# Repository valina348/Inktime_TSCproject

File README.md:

# InkTime Smartwatch

> An open-source, low-cost smartwatch built around the nRF52840 SoC and an e-paper display.

---

## Block Diagram

```
                        ┌─────────────────────────────────────────────────────┐
                        │                   nRF52840 (U1)                     │
                        │              ARM Cortex-M4F @ 64 MHz                │
                        │           BLE 5.0 | USB 2.0 FS | SWD               │
                        └──┬──────┬──────┬──────┬──────┬──────┬──────┬───────┘
                           │ SPI  │ I2C  │ I2C  │ I2C  │ I2C  │GPIO  │ USB
                           │      │      │      │      │      │      │
              ┌────────────┘      │      │      │      │      │      └──────────────┐
              │                   │      │      │      │      │                     │
        ┌─────▼──────┐     ┌──────▼─┐ ┌─▼────┐ │  ┌───▼───┐  │              ┌─────▼──────┐
        │  WSH-12561 │     │BMA421  │ │MAX   │ │  │DRV2605│  │              │KH-TYPE-C   │
        │  E-Paper   │     │  IMU   │ │17048 │ │  │Haptic │  │              │  USB-C     │
        │  Display   │     │ 6-axis │ │Fuel  │ │  │Driver │  │              │ Connector  │
        └────────────┘     └────────┘ │Gauge │ │  └───┬───┘  │              └─────┬──────┘
                                      └──────┘ │      │      │                    │
                                               │  ┌───▼───┐  │              ┌─────▼──────┐
                                               │  │FIT0774│  │              │USBLC6-2SC6Y│
                                        I2C    │  │ ERM   │  │              │ESD Protect │
                                        │      │  │ Motor │  │              └─────┬──────┘
                                        │      │  └───────┘  │                    │
                                  ┌─────▼──────────────────┐ │              ┌─────▼──────┐
                                  │    BQ25180YBGR         │ │              │   VBUS     │
                                  │    LiPo Charger        │◄┘              │  detect    │
                                  └─────┬──────────────────┘                └────────────┘
                                        │
                              ┌─────────▼──────────┐
                              │  AKY0106 LiPo Bat  │
                              │  400 mAh / 3.7V    │
                              └─────────┬──────────┘
                                        │ VBAT
                              ┌─────────▼──────────┐
                              │   RT6160AWSC        │
                              │   Boost Converter   │
                              │  (EPD HV supply)    │
                              └─────────────────────┘

External:
  32.768 kHz Crystal ──► nRF52840 (LFXO — RTC)
  2450AT18B100E Ant  ──► nRF52840 (RF pin, via matching network)
  TC2030-IDC         ──► nRF52840 (SWD debug)
  3x Tactile Buttons ──► nRF52840 (GPIO, active low)
```

---

## Bill of Materials (BOM)

| Ref | Component | Description | Package | Qty | JLCPCB | Datasheet |
|-----|-----------|-------------|---------|-----|--------|-----------|
| U1 | nRF52840-QIAA | MCU, BLE 5.0, ARM Cortex-M4F, 1MB Flash, 256KB RAM | QFN-73 | 1 | [C190794](https://jlcpcb.com/partdetail/NordicSemiconductor-nRF52840_QIAA/C190794) | [Datasheet](https://infocenter.nordicsemi.com/pdf/nRF52840_PS_v1.7.pdf) |
| U2 | BQ25180YBGR | LiPo charger, I2C, 1A, integrated power path | DSBGA-9 | 1 | [C2678722](https://jlcpcb.com/partdetail/TexasInstruments-BQ25180YBGR/C2678722) | [Datasheet](https://www.ti.com/lit/ds/symlink/bq25180.pdf) |
| U3 | MAX17048G+T10 | Fuel gauge, 1% SOC accuracy, I2C | SOT-23-6 | 1 | [C82344](https://jlcpcb.com/partdetail/MaximIntegrated-MAX17048G_T10/C82344) | [Datasheet](https://datasheets.maximintegrated.com/en/ds/MAX17048-MAX17049.pdf) |
| U4 | RT6160AWSC | DC/DC boost converter for EPD supply | SOT-23-6 | 1 | [Search RT6160AWSC](https://jlcpcb.com/parts/componentSearch?searchTxt=RT6160AWSC) | [Datasheet](https://www.richtek.com/assets/product_file/RT6160A/DS6160A-00.pdf) |
| U5 | DRV2605YZFR | Haptic driver, I2C, LRA/ERM support | DSBGA-16 | 1 | [C2062186](https://jlcpcb.com/partdetail/TexasInstruments-DRV2605YZFR/C2062186) | [Datasheet](https://www.ti.com/lit/ds/symlink/drv2605.pdf) |
| IC1 | BMA421 | 6-axis IMU, accelerometer + gyroscope, I2C | LGA-12 | 1 | [Search BMA421](https://jlcpcb.com/parts/componentSearch?searchTxt=BMA421) | [Datasheet](https://www.bosch-sensortec.com/media/boschsensortec/downloads/datasheets/bst-bma421-ds000.pdf) |
| IC2 | USBLC6-2SC6Y | USB ESD protection | SOT-363 | 1 | [C2827654](https://jlcpcb.com/partdetail/STMicroelectronics-USBLC6_2SC6Y/C2827654) | [Datasheet](https://www.st.com/resource/en/datasheet/usblc6-2.pdf) |
| J1 | KH-TYPE-C-16P | USB-C connector, 16-pin | SMD | 1 | [Search KH-TYPE-C-16P](https://jlcpcb.com/parts/componentSearch?searchTxt=KH-TYPE-C-16P) | - |
| J2 | TC2030-IDC | Tag-Connect SWD debug connector, 10-pin | THT | 1 | - | [Datasheet](https://www.tag-connect.com/wp-content/uploads/bsk-pdf-manager/TC2030-IDC_1.pdf) |
| ANT1 | 2450AT18B100E | 2.4 GHz chip antenna, 50 Ω | SMD | 1 | [Search 2450AT18B100E](https://jlcpcb.com/parts/componentSearch?searchTxt=2450AT18B100E) | [Datasheet](https://www.johansontechnology.com/datasheets/2450AT18B100E/2450AT18B100E.pdf) |
| L1 | FTC252012SR47MBCA | Power inductor 4.7 µH | 1008 | 1 | [Search FTC252012SR47M](https://jlcpcb.com/parts/componentSearch?searchTxt=FTC252012SR47M) | - |
| L2 | - | Inductor 10 µH (DC/DC) | 0402 | 1 | - | - |
| L3 | - | Inductor 15 nH (RF matching) | 0402 | 1 | - | - |
| L7 | - | Inductor 3.9 nH (antenna matching) | 0402 | 1 | - | - |
| M1 | DFRobot FIT0774 | ERM haptic motor (shaker) | - | 1 | - | [Datasheet](https://wiki.dfrobot.com/Vibration_Motor_SKU__FIT0774) |
| BAT1 | AKY0106 | LiPo battery 400 mAh, 3.7V | - | 1 | - | - |
| DSP1 | WSH-12561 | E-paper display, SPI interface | - | 1 | - | - |
| X1 | - | Crystal 32.768 kHz | SMD | 1 | - | - |
| SW1–SW3 | - | Tactile push button | SMD | 3 | - | - |
| R1–Rn | - | Resistors, various values | 0201 | - | - | - |
| C1–Cn | - | Capacitors ≤100nF → 0201, >100nF → 0402 | 0201/0402 | - | - | - |

---

## Hardware Description

### MCU — nRF52840 (U1)

The nRF52840 is the central processing unit of InkTime. It integrates:

- ARM Cortex-M4F running at 64 MHz with hardware FPU
- Bluetooth Low Energy 5.0 (used for time synchronization and smartphone notifications)
- USB 2.0 Full Speed (charging detection and firmware updates over DFU)
- 1 MB Flash / 256 KB RAM
- Multiple hardware peripherals: SPI, I2C, UART, ADC, PWM, RTC

All peripherals connect directly to the nRF52840:
- **SPI** — e-paper display (WSH-12561)
- **I2C** — IMU (BMA421), fuel gauge (MAX17048), LiPo charger (BQ25180), haptic driver (DRV2605)
- **GPIO** — buttons, EPD control lines, interrupt lines, HAPTIC_EN

A 32.768 kHz crystal (X1) is connected to XL1/XL2 pins to drive the internal low-frequency oscillator (LFXO), used for the real-time clock (RTC) and sleep timers with µA-level current consumption.

---

### Power Path

```
USB-C (VBUS 5V)
    └──► BQ25180YBGR (LiPo charger, up to 1A)
              ├──► AKY0106 LiPo Battery (400 mAh, 3.7V)
              └──► 3.3V rail (VREG) ──► nRF52840 + all peripherals

VBAT (3.7V from battery)
    └──► RT6160AWSC (boost converter)
              └──► EPD high-voltage supply (PREVGH, PREVGL, GDR, VCOM)
```

**BQ25180YBGR** manages LiPo charging with integrated power path — the system can run from USB while simultaneously charging the battery. It communicates with the MCU over I2C and raises the `PMIC_INT` line on fault or status events (charge complete, overtemperature, etc.).

**RT6160AWSC** is a boost converter that generates the higher voltages required by the e-paper display driver circuit. The EPD requires both positive and negative rail voltages (PREVGH ≈ +20V, PREVGL ≈ −20V) for bistable switching of the electrophoretic ink particles.

**MAX17048G+T10** is a ModelGauge fuel gauge that estimates battery state-of-charge (SOC) with 1% accuracy using a single-cell LiPo model, communicating over I2C. It raises an `ALERT` interrupt when the battery falls below a programmable low-threshold.

---

### E-Paper Display — WSH-12561

The e-paper display uses SPI communication plus 3 control GPIO lines:

| Signal | Direction | Description |
|--------|-----------|-------------|
| SCK | MCU → EPD | SPI clock |
| MOSI | MCU → EPD | SPI data (write only) |
| EPD_CS | MCU → EPD | Chip select (active low) |
| EPD_DC | MCU → EPD | Data / Command select |
| EPD_RST | MCU → EPD | Hardware reset (active low) |
| EPD_BUSY | EPD → MCU | Busy flag — MCU must wait before next command |

The EPD drive circuit (powered by RT6160AWSC boost converter) generates PREVGH, PREVGL, and GDR voltages needed to drive the bistable ink display. A MOSFET (Q3 — DMG2305UX) gates the EPD power supply so it can be fully cut when the display is not refreshing, saving power.

E-paper is chosen for InkTime because it consumes power **only during refresh** (not while displaying a static image), making it ideal for a low-power wearable.

---

### IMU — BMA421

6-axis inertial measurement unit connected via I2C at 400 kHz. Provides:
- 3-axis accelerometer — step counting, gesture detection, tilt/orientation
- 3-axis gyroscope — motion tracking, wrist-raise detection
- Two interrupt lines (`IMU_INT1`, `IMU_INT2`) for wake-on-motion and data-ready events

The IMU is configured for I2C mode by pulling `CSB` high (to 3V3). The I2C address is set via the `SDO` pin (GND = 0x18, 3V3 = 0x19).

---

### Haptic Feedback — DRV2605 + FIT0774

The DRV2605YZFR haptic driver controls the FIT0774 ERM (eccentric rotating mass) vibration motor. It connects to the MCU over I2C and is enabled via the `HAPTIC_EN` GPIO. The driver supports 124 built-in haptic waveform effects (notification patterns, alerts, confirmations) without requiring MCU intervention during playback.

---

### USB — KH-TYPE-C-16P + USBLC6-2SC6Y

USB-C connector with USBLC6-2SC6Y ESD protection on D+ and D− lines. CC1 and CC2 pins each have a 5.1 kΩ pull-down resistor to GND, which is mandatory for USB-C devices to be recognized as UFP (Upstream Facing Port / device) by USB-C chargers and hosts.

The nRF52840 detects VBUS presence via a GPIO to hand off charging control to the BQ25180. USB D+/D− connect directly to the nRF52840's integrated USB transceiver for DFU (Device Firmware Update) support.

---

### Antenna — 2450AT18B100E

2.4 GHz chip antenna placed at the edge of the PCB. Design rules followed:
- No copper pours (ground plane or power planes) under the antenna keepout area
- No signal traces routed under the antenna
- PCB cutout under the antenna to reduce parasitic capacitance to ground
- Pi-network impedance matching (inductor + two capacitors) between the nRF52840 RF pin and the antenna feed, targeting 50 Ω impedance match at 2.4 GHz

---

### SWD Debug — TC2030-IDC

Tag-Connect TC2030-IDC footprint for in-circuit programming and debugging. No physical connector is soldered — a spring-loaded probe clips onto the 6 pads. Test pads are exposed and labeled in silkscreen:

| Test Pad | Signal |
|----------|--------|
| TP_SWDIO | SWDIO |
| TP_SWDCLK | SWDCLK |
| TP_RESET | RESET |
| TP_3.3V | 3V3 |
| TP_GND | GND |
| TP_SWO | SWO (trace output) |

---

## nRF52840 Pin Assignment

| Pin | Net | Connected To | Interface | Notes |
|-----|-----|--------------|-----------|-------|
| P0.00 | XL1 | 32.768 kHz crystal | LFXO | Low-frequency clock for RTC |
| P0.01 | XL2 | 32.768 kHz crystal | LFXO | Low-frequency clock for RTC |
| P0.09 | RF/ANT | Antenna matching network → ANT1 | RF | Dedicated RF pin — PCB cutout required |
| P0.13 | BTN1 | Tactile button SW_UP | GPIO | Active low, 10K pull-up, 1µF debounce |
| P0.14 | BTN2 | Tactile button SW_DN | GPIO | Active low, 10K pull-up, 1µF debounce |
| P0.26 | BTN3 | Tactile button SW_ENT | GPIO | Active low, 10K pull-up, 1µF debounce |
| P0.xx | SDA | BMA421, MAX17048, BQ25180, DRV2605 | I2C | Shared bus, 4.7 kΩ pull-up to 3V3 |
| P0.xx | SCL | BMA421, MAX17048, BQ25180, DRV2605 | I2C | Shared bus, 4.7 kΩ pull-up to 3V3 |
| P1.xx | SCK | E-paper display (WSH-12561) | SPI | |
| P1.xx | MOSI | E-paper display (WSH-12561) | SPI | |
| P1.xx | EPD_CS | E-paper chip select | GPIO | Active low |
| P1.xx | EPD_DC | E-paper data/command | GPIO | High = data, Low = command |
| P1.xx | EPD_RST | E-paper reset | GPIO | Active low |
| P1.xx | EPD_BUSY | E-paper busy flag | GPIO input | MCU polls or uses interrupt |
| P1.xx | HAPTIC_EN | DRV2605 enable | GPIO | Active high |
| P1.xx | PMIC_INT | BQ25180 interrupt | GPIO input | Active low, fault/status events |
| P1.xx | IMU_INT1 | BMA421 interrupt 1 | GPIO input | Wake-on-motion |
| P1.xx | IMU_INT2 | BMA421 interrupt 2 | GPIO input | Data ready |
| P1.xx | ALERT | MAX17048 alert | GPIO input | Low battery threshold |
| SWDIO | SWDIO | TC2030 pin 2 / TP_SWDIO | SWD | Programming & debug |
| SWDCLK | SWDCLK | TC2030 pin 4 / TP_SWDCLK | SWD | Programming & debug |
| D+ | D+ | USB-C D+ (via USBLC6 ESD) | USB | Full-speed USB transceiver |
| D− | D− | USB-C D− (via USBLC6 ESD) | USB | Full-speed USB transceiver |
| VBUS | VBUS | USB-C VBUS detect | GPIO input | 5V presence detection |

> **Note:** Pins marked `P0.xx` / `P1.xx` are assigned in firmware and will be finalized in the GNG revision. The I2C bus is shared between BMA421, MAX17048, BQ25180, and DRV2605 — each has a unique I2C address.

---

## Power Consumption Estimates

| State | Active Components | Estimated Current |
|-------|-------------------|-------------------|
| Deep sleep | nRF52840 RTC only | ~3 µA |
| BLE advertising | MCU + BLE radio | ~3 mA avg |
| E-paper refresh | MCU + EPD + boost converter | ~30 mA peak (1–2 s) |
| IMU active | MCU + IMU | ~1.5 mA |
| Full operation (BLE + EPD + IMU) | All | ~35 mA peak |

**Battery life estimate** (400 mAh, typical usage: BLE advertising + sleep + 1 EPD refresh/min):

```
Average current ≈ 3 mA (BLE) × 10% duty + 3 µA × 90% + 30 mA × (2s/60s)
               ≈ 0.3 mA + 0.003 mA + 1 mA
               ≈ ~1.3 mA average

Battery life ≈ 400 mAh / 1.3 mA ≈ ~13 days
```

---

## Design Log

### PCB Design Decisions

- **4-layer stackup** used to allow a dedicated ground plane on an inner layer, improving RF performance and reducing EMI near the BLE antenna.
- **Antenna placement** at the top edge of the PCB with a copper-free keepout zone and PCB cutout beneath it, per the 2450AT18B100E datasheet recommendations.
- **Decoupling capacitors** (100 nF, 0201) placed as close as possible to each VDD/VDDH/DEC pin of the nRF52840, per Nordic's hardware design guide.
- **Via stitching** applied between top and bottom ground planes, especially around the RF section, to minimize ground impedance at RF frequencies.
- **All components placed on TOP layer** only, as required by the project specification.
- **Power traces** routed at 0.3 mm width (VCC, VBUS, VBAT, 3V3); signal traces at minimum 0.15 mm.
- **No right-angle bends** on any trace — all routing uses 45° angles.
- **USB-C CC resistors** (5.1 kΩ to GND on CC1 and CC2) ensure correct USB-C device recognition by any standard charger.
- **Battery connected directly to test pads** (TP_VBAT, TP_BAT_GND) on the PCB instead of using the JST connector, to save vertical space inside the enclosure.

### Known Accepted Errors

- DRC "Dimension" errors caused by the placement of the three tactile buttons and the USB-C connector at the PCB edge — these are by design to align with the physical openings in the enclosure and are accepted per project specification.
- ERC warning "Only INPUT pins on NET ID" — accepted per project specification (known Fusion360 library artifact).

---

## License

This project is licensed under the **Apache License 2.0**.

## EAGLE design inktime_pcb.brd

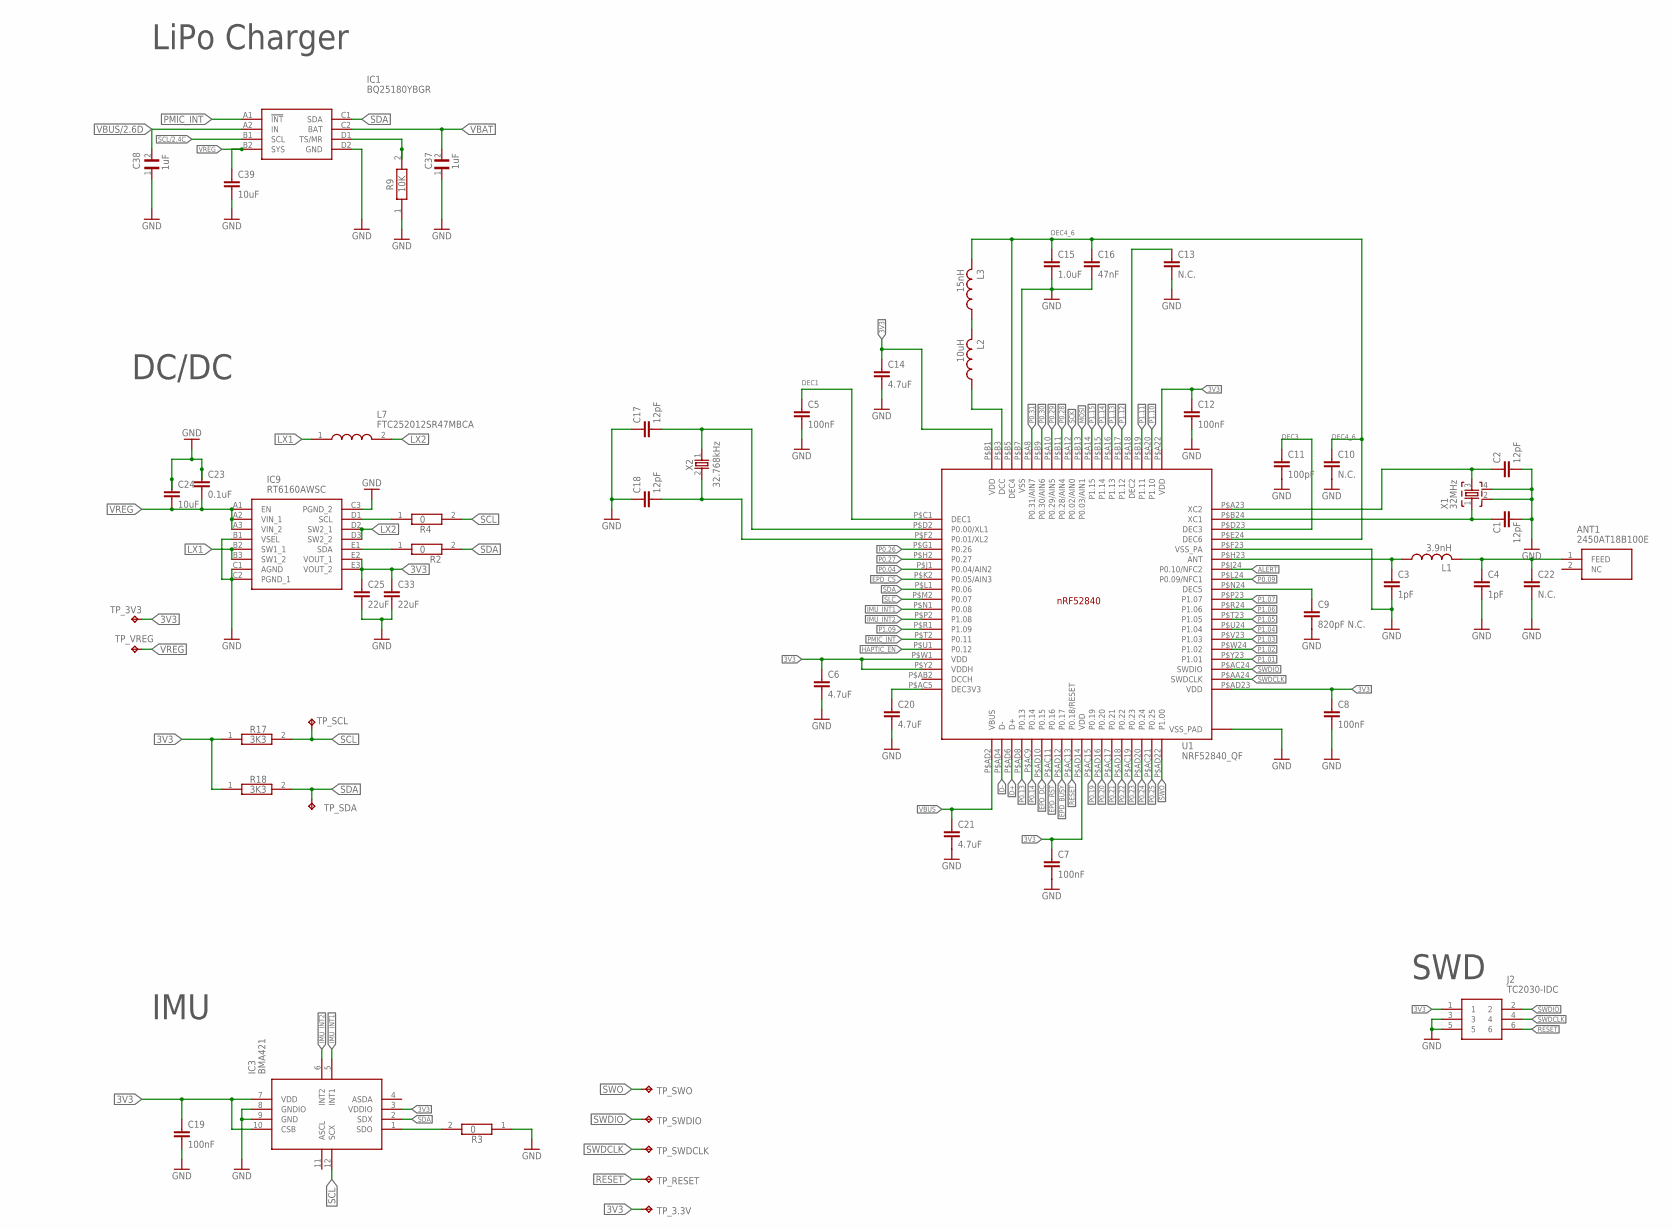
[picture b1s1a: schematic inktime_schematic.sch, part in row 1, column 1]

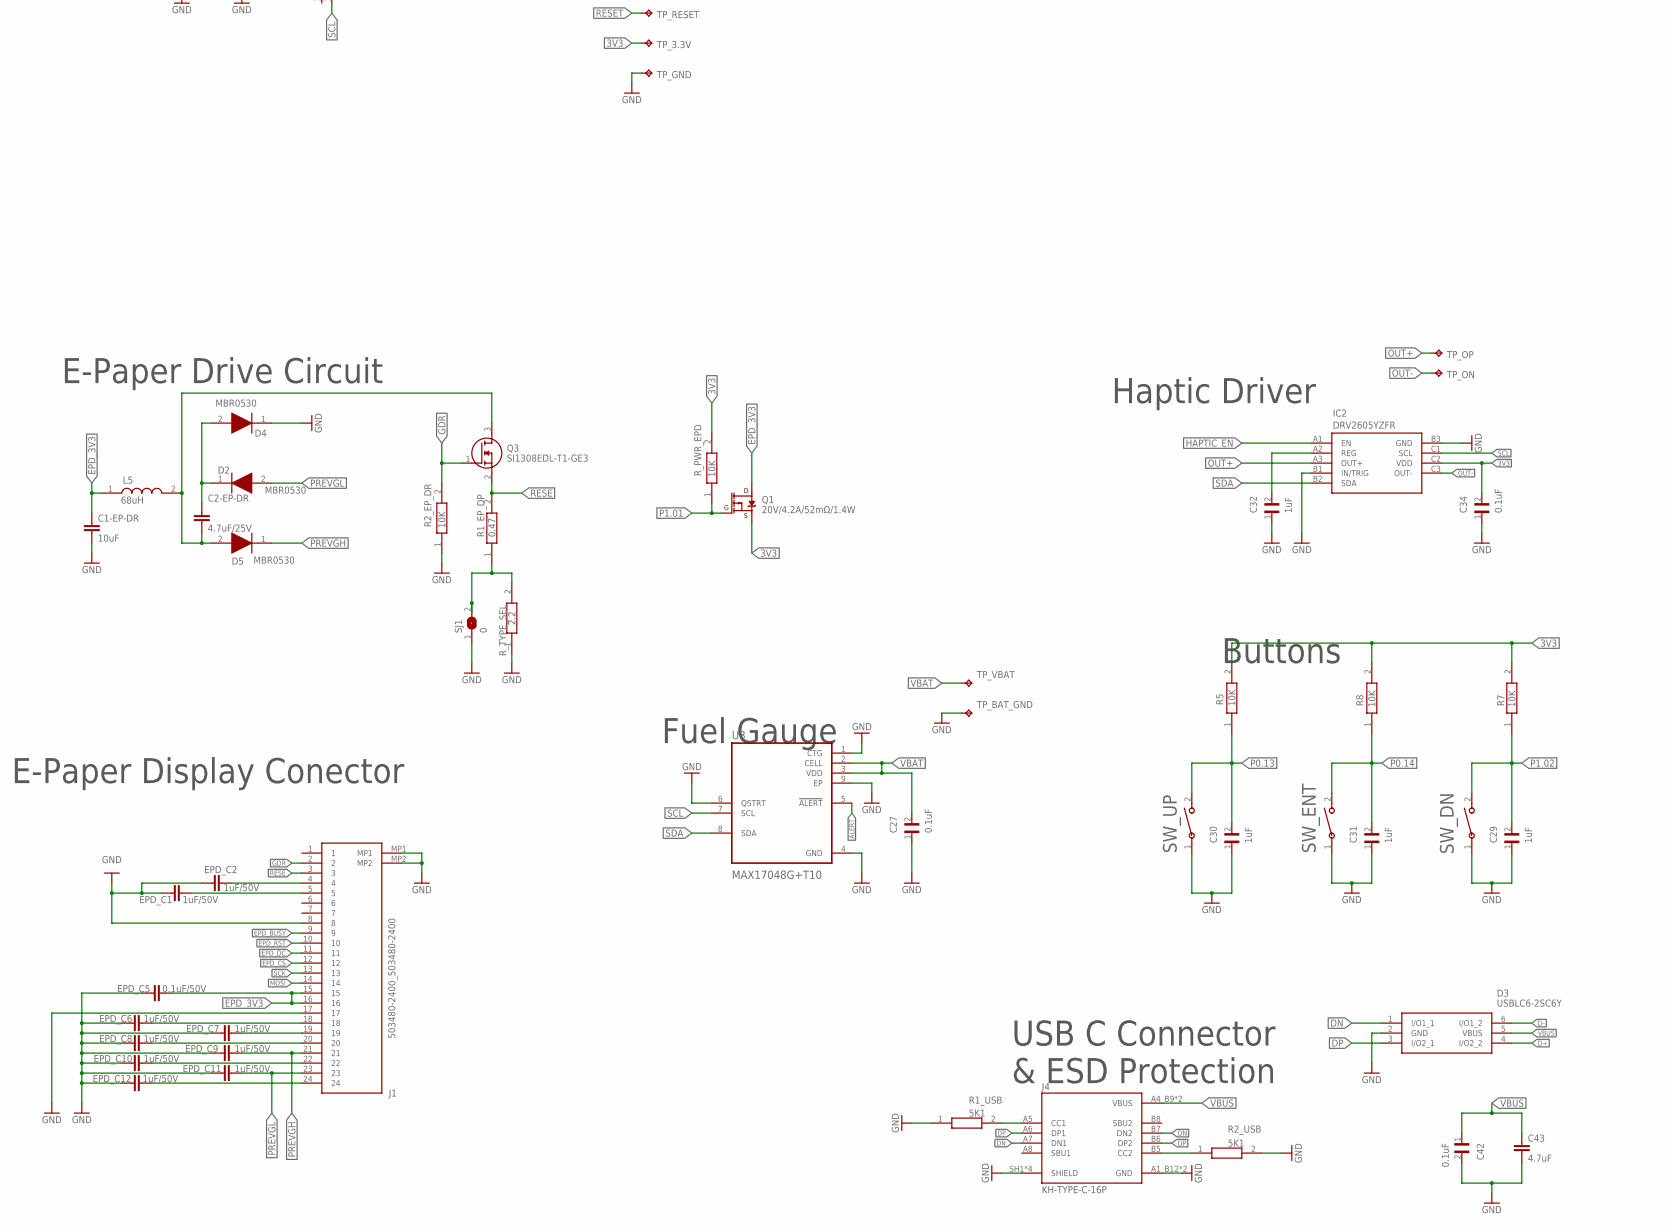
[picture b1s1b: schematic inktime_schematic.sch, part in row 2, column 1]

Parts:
ANT1: 2450AT18B100E; 2450AT18B100E_ANTC3216X140N
C1, C2, C17, C18: 12pF; NORDIC_NRF_3_RESC0201_L
C1-EP-DR, C24, C39: 10uF; NORDIC_NRF_3_RESC0201_L
C2-EP-DR: 4.7uF/25V; NORDIC_NRF_3_RESC0201_L
C3, C4: 1pF; NORDIC_NRF_3_RESC0201_L
C5, C7, C8, C12, C19: 100nF; NORDIC_NRF_3_RESC0201_L
C6, C14, C20, C21, C43: 4.7uF; NORDIC_NRF_3_RESC0201_L
C9: 820pF N.C.; NORDIC_NRF_3_RESC0201_L
C10, C13, C22: N.C.; NORDIC_NRF_3_RESC0201_L
C11: 100pF; NORDIC_NRF_3_RESC0201_L
C15: 1.0uF; NORDIC_NRF_3_RESC0201_L
C16: 47nF; NORDIC_NRF_3_RESC0201_L
C23: 0.1uF; NORDIC_NRF_3_RESC0201_L
C25, C33: 22uF; NORDIC_NRF_3_RESC0201_L
C27, C34, C42: 0.1uF; GRM011R60J152KE01L_2_CAPC0201X13N
C29, C30, C31, C32, C37, C38: 1uF; GRM011R60J152KE01L_2_CAPC0201X13N
D2, D4, D5: MBR0530; ESP32_C6_LIBRARY_5_SOD3716X135N
D3: USBLC6-2SC6Y; ESP32_C6_LIBRARY_3_SOT95P280X145-6N
EPD_C1, EPD_C2, EPD_C6, EPD_C7, EPD_C8, EPD_C9, EPD_C10, EPD_C11, EPD_C12: 1uF/50V; NORDIC_NRF_3_RESC0201_L
EPD_C5: 0.1uF/50V; NORDIC_NRF_3_RESC0201_L
IC1: BQ25180YBGR; BQ25180YBGR_BGA8C40P2X4_100X155X50
IC2: DRV2605YZFR; DRV2605YZFR_BGA9C50P3X3_144X144X62
IC3: BMA421; BMA423_BMA423
IC9: RT6160AWSC; RT6160AWSC_BGA15C40P3X5_140X230X60
J1: 503480-2400_503480-2400; 503480-2400_5034802400
J2: TC2030-IDC; TC2030-IDC_TC2030IDC
J4: KH-TYPE-C-16P; KH-TYPE-C-16P_KINGHELM_KH-TYPE-C-16P
L1: 3.9nH; NORDIC_NRF_2_RESC0402_L
L2: 10uH; NORDIC_NRF_2_RESC0402_L
L3: 15nH; NORDIC_NRF_2_RESC0402_L
L5: 68uH; MLP2016SR47MT0S1_INDC2016X100N
L7: FTC252012SR47MBCA; MLP2016SR47MT0S1_INDC2016X100N
Q1: 20V/4.2A/52mΩ/1.4W; ESP32_C6_LIBRARY_4_ESP32_C6_LIBRARY_4_ESP32_C6_LIBRARY_4_ES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
Q3: SI1308EDL-T1-GE3; ESP32_C6_LIBRARY_6_SOT65P210X110-3N
R1_EP_DP: 0.47; CPF0201D7K68C1_0201
R1_USB, R2_USB: 5K1; CPF0201D7K68C1_0201
R2, R3, R4: 0; CPF0201D7K68C1_0201
R2_EP_DR, R5, R7, R8, R9: 10K; CPF0201D7K68C1_0201
R17, R18: 3K3; CPF0201D7K68C1_0201
R_PWR_EPD: 10K; CPF0201D7K68C1_0201
R_TYPE_SEL: 2.2; CPF0201D7K68C1_0201
SJ1: 0; ESP32_C6_LIBRARY_7_JUMPER_SJ
SW_DN: 2025-10-22_07-23-44_LIBRARY_EVP-AKE31ASW_EVP-AKE3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; 2025-10-22_07-23-44_LIBRARY_SW_EVP-AKE31A_PAN
SW_ENT: 2025-10-22_07-23-44_LIBRARY_EVP-AKE31ASW_EVP-AKE3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; 2025-10-22_07-23-44_LIBRARY_SW_EVP-AKE31A_PAN
SW_UP: 2025-10-22_07-23-44_LIBRARY_EVP-AKE31ASW_EVP-AKE3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; 2025-10-22_07-23-44_LIBRARY_SW_EVP-AKE31A_PAN
TP_3.3V, TP_3V3: HECTOR_WATCH_1_TPTP20R; HECTOR_WATCH_1_TP20R
TP_BAT_GND: HECTOR_WATCH_1_TPTP20R; HECTOR_WATCH_1_TP20R
TP_GND: HECTOR_WATCH_1_TPTP20R; HECTOR_WATCH_1_TP20R
TP_ON: HECTOR_WATCH_1_TPTP20R; HECTOR_WATCH_1_TP20R
TP_OP: HECTOR_WATCH_1_TPTP20R; HECTOR_WATCH_1_TP20R
TP_RESET: HECTOR_WATCH_1_TPTP20R; HECTOR_WATCH_1_TP20R
TP_SCL: HECTOR_WATCH_1_TPTP20R; HECTOR_WATCH_1_TP20R
TP_SDA: HECTOR_WATCH_1_TPTP20R; HECTOR_WATCH_1_TP20R
TP_SWDCLK: HECTOR_WATCH_1_TPTP20R; HECTOR_WATCH_1_TP20R
TP_SWDIO: HECTOR_WATCH_1_TPTP20R; HECTOR_WATCH_1_TP20R
TP_SWO: HECTOR_WATCH_1_TPTP20R; HECTOR_WATCH_1_TP20R
TP_VBAT: HECTOR_WATCH_1_TPTP20R; HECTOR_WATCH_1_TP20R
TP_VREG: HECTOR_WATCH_1_TPTP20R; HECTOR_WATCH_1_TP20R
U1: NRF52840_QF; NORDIC_NRF_4_AQFN50P700X700X85_HS-74N
U3: MAX17048G+T10; ESP32_C6_LIBRARY_SON50P200X200X80-9N
X1: 32MHz; NORDIC_NRF_BT-XTAL_2016_N
X2: 32.768kHz; NORDIC_NRF_1_XTAL_3215_N

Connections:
3V3: C6.1, C7.1, C8.1, C12.1, C14.1, C19.1, C25.1, C33.1, C34.2, IC2.C2 (VDD), IC3.3 (VDDIO), IC3.7 (VDD), IC3.10 (CSB), IC9.E2 (VOUT_1), IC9.E3 (VOUT_2), J2.1, Q1.2 (S), R5.2, R7.2, R8.2, R17.1, R18.1, R_PWR_EPD.2, TP_3.3V.TP, TP_3V3.TP, U1.P$A22 (VDD), U1.P$AD14 (VDD), U1.P$AD23 (VDD), U1.P$B1 (VDD), U1.P$W1 (VDD), U1.P$Y2 (VDDH)
ALERT: U1.P$J24 (P0.10/NFC2), U3.5 (!ALERT)
D+: D3.4 (I/O2_2), U1.P$AD6 (D+)
D-: D3.6 (I/O1_2), U1.P$AD4 (D-)
DEC1: C5.1, U1.P$C1 (DEC1)
DEC3: C11.1, U1.P$D23 (DEC3)
DEC4_6: C10.1, C15.1, C16.1, L3.2, U1.P$B5 (DEC4), U1.P$E24 (DEC6)
DN: D3.1 (I/O1_1), J4.A7 (DN1), J4.B7 (DN2)
DP: D3.3 (I/O2_1), J4.A6 (DP1), J4.B6 (DP2)
EPD_3V3: C1-EP-DR.1, EPD_C5.2, J1.15, J1.16, L5.1, Q1.3 (D)
EPD_BUSY: J1.9, U1.P$AD12 (P0.17)
EPD_CS: J1.12, U1.P$K2 (P0.05/AIN3)
EPD_DC: J1.11, U1.P$AD10 (P0.15)
EPD_RST: J1.10, U1.P$AC11 (P0.16)
GDR: J1.2, Q3.1 (G), R2_EP_DR.2
GND: C1.2, C1-EP-DR.2, C2.2, C3.2, C4.2, C5.2, C6.2, C7.2, C8.2, C9.2, C10.2, C11.2, C12.2, C13.2, C14.2, C15.2, C16.2, C17.1, C18.1, C19.2, C20.2, C21.2, C22.2, C23.1, C24.1, C25.2, C27.1, C29.1, C30.1, C31.1, C32.1, C33.2, C34.1, C37.1, C38.1, C39.2, C42.2, C43.2, D3.2 (GND), D4.1 (K), EPD_C1.1, EPD_C2.1, EPD_C5.1, EPD_C6.1, EPD_C7.1, EPD_C8.1, EPD_C9.1, EPD_C10.1, EPD_C11.1, EPD_C12.1, IC1.D2 (GND), IC2.B1 (IN/TRIG), IC2.B3 (GND), IC3.8 (GNDIO), IC3.9 (GND), IC9.B1 (VSEL), IC9.C1 (AGND), IC9.C2 (PGND_1), IC9.C3 (PGND_2), J1.8, J1.17, J1.MP1, J1.MP2, J2.3, J2.5, J4.A1_B12 (GND), J4.A12_B1 (GND), J4.SH1 (SHIELD), J4.SH2 (SHIELD), J4.SH3 (SHIELD), J4.SH4 (SHIELD), R1_USB.1, R2_EP_DR.1, R2_USB.2, R3.1, R9.1, R_TYPE_SEL.1, SJ1.1, SW_DN.1, SW_ENT.1, SW_UP.1, TP_BAT_GND.TP, TP_GND.TP, U1.P$74 (VSS_PAD), U1.P$75 (VSS_PAD), U1.P$76 (VSS_PAD), U1.P$77 (VSS_PAD), U1.P$78 (VSS_PAD), U1.P$79 (VSS_PAD), U1.P$80 (VSS_PAD), U1.P$81 (VSS_PAD), U1.P$82 (VSS_PAD), U1.P$83 (VSS_PAD), U1.P$84 (VSS_PAD), U1.P$85 (VSS_PAD), U1.P$86 (VSS_PAD), U1.P$87 (VSS_PAD), U1.P$88 (VSS_PAD), U1.P$89 (VSS_PAD), U1.P$90 (VSS_PAD), U1.P$B7 (VSS), U1.P$F23 (VSS_PA), U3.1 (CTG), U3.4 (GND), U3.6 (QSTRT), U3.9 (EP), X1.2, X1.4
HAPTIC_EN: IC2.A1 (EN), U1.P$U1 (P0.12)
IMU_INT1: IC3.5 (INT1), U1.P$N1 (P0.08)
IMU_INT2: IC3.6 (INT2), U1.P$P2 (P1.08)
LX1: IC9.B2 (SW1_1), IC9.B3 (SW1_2), L7.1
LX2: IC9.D2 (SW2_1), IC9.D3 (SW2_2), L7.2
MOSI: J1.14, U1.P$B13 (P0.03/AIN1)
unnamed: IC1.D1 (TS/MR), R9.2
unnamed: C2-EP-DR.1, D2.1 (K), D4.2 (A)
unnamed: IC9.D1 (SCL), R4.1
unnamed: C2-EP-DR.2, D5.2 (A), L5.2, Q3.3 (D)
unnamed: IC9.E1 (SDA), R2.1
unnamed: IC3.1 (SDO), R3.2
unnamed: R1_EP_DP.1, R_TYPE_SEL.2, SJ1.2
unnamed: EPD_C2.2, J1.4
unnamed: EPD_C1.2, J1.5
unnamed: EPD_C6.2, J1.18
unnamed: EPD_C7.2, J1.19
unnamed: EPD_C8.2, J1.20
unnamed: C32.2, IC2.A2 (REG)
unnamed: EPD_C10.2, J1.22
unnamed: J4.A5 (CC1), R1_USB.2
unnamed: EPD_C12.2, J1.24
unnamed: J4.B5 (CC2), R2_USB.1
unnamed: C3.1, L1.1, U1.P$H23 (ANT)
unnamed: ANT1.1 (FEED), C4.1, C22.1, L1.2
unnamed: C1.1, U1.P$B24 (XC1), X1.1
unnamed: C2.1, U1.P$A23 (XC2), X1.3
unnamed: C20.1, U1.P$AC5 (DEC3V3)
unnamed: C13.1, U1.P$A18 (DEC2)
unnamed: L2.1, U1.P$B3 (DCC)
unnamed: L2.2, L3.1
unnamed: C9.1, U1.P$N24 (DEC5)
unnamed: C18.2, U1.P$F2 (P0.01/XL2), X2.2
unnamed: C17.2, U1.P$D2 (P0.00/XL1), X2.1
OUT+: IC2.A3 (OUT+), TP_OP.TP
OUT-: IC2.C3 (OUT-), TP_ON.TP
P0.04: U1.P$J1 (P0.04/AIN2)
P0.09: U1.P$L24 (P0.09/NFC1)
P0.13: C30.2, R5.1, SW_UP.2, U1.P$AD8 (P0.13)
P0.14: C31.2, R8.1, SW_ENT.2, U1.P$AC9 (P0.14)
P0.19: U1.P$AC15 (P0.19)
P0.20: U1.P$AD16 (P0.20)
P0.21: U1.P$AC17 (P0.21)
P0.22: U1.P$AD18 (P0.22)
P0.23: U1.P$AC19 (P0.23)
P0.24: U1.P$AD20 (P0.24)
P0.25: U1.P$AC21 (P0.25)
P0.26: U1.P$G1 (P0.26)
P0.27: U1.P$H2 (P0.27)
P0.28: U1.P$B11 (P0.28/AIN4)
P0.29: U1.P$A10 (P0.29/AIN5)
P0.30: U1.P$B9 (P0.30/AIN6)
P0.31: U1.P$A8 (P0.31/AIN7)
P1.01: Q1.1 (G), R_PWR_EPD.1, U1.P$Y23 (P1.01)
P1.02: C29.2, R7.1, SW_DN.2, U1.P$W24 (P1.02)
P1.03: U1.P$V23 (P1.03)
P1.04: U1.P$U24 (P1.04)
P1.05: U1.P$T23 (P1.05)
P1.06: U1.P$R24 (P1.06)
P1.07: U1.P$P23 (P1.07)
P1.09: U1.P$R1 (P1.09)
P1.10: U1.P$A20 (P1.10)
P1.11: U1.P$B19 (P1.11)
P1.12: U1.P$B17 (P1.12)
P1.13: U1.P$A16 (P1.13)
P1.14: U1.P$B15 (P1.14)
P1.15: U1.P$A14 (P1.15)
PMIC_INT: IC1.A1 (!INT), U1.P$T2 (P0.11)
PREVGH: D5.1 (K), EPD_C9.2, J1.21
PREVGL: D2.2 (A), EPD_C11.2, J1.23
RESE: J1.3, Q3.2 (S), R1_EP_DP.2
RESET: J2.6, TP_RESET.TP, U1.P$AC13 (P0.18/RESET)
SCK: J1.13, U1.P$A12 (P0.02/AIN0)
SDA: IC1.C1 (SDA), IC2.B2 (SDA), IC3.2 (SDX), R2.2, R18.2, TP_SDA.TP, U1.P$L1 (P0.06), U3.8 (SDA)
SWDCLK: J2.4, TP_SWDCLK.TP, U1.P$AA24 (SWDCLK)
SWDIO: J2.2, TP_SWDIO.TP, U1.P$AC24 (SWDIO)
SWO: TP_SWO.TP, U1.P$AD22 (P1.00)
VBAT: C27.2, C37.2, IC1.C2 (BAT), TP_VBAT.TP, U3.2 (CELL), U3.3 (VDD)
VREG: C23.2, C24.2, C39.1, IC1.B2 (SYS), IC9.A1 (EN), IC9.A2 (VIN_1), IC9.A3 (VIN_2), TP_VREG.TP

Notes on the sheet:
LiPo Charger
DC/DC
IMU
SWD
E-Paper Drive Circuit
Fuel Gauge
E-Paper Display Conector
Haptic Driver
Buttons
USB C Connector & ESD Protection

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
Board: 4 copper layers, 105 parts (0 on the bottom side), 71 nets, no tracks yet.

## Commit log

2026-04-16 Project Final
2026-04-16 Final Project

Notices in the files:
parts and their libraries:
InkTime_v5: COPYRIGHT: Copyright (C) 2025 Ultra Librarian. All rights reserved.
